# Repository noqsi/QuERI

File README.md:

# QuERI
Electronics for X-ray fluorescence measurements

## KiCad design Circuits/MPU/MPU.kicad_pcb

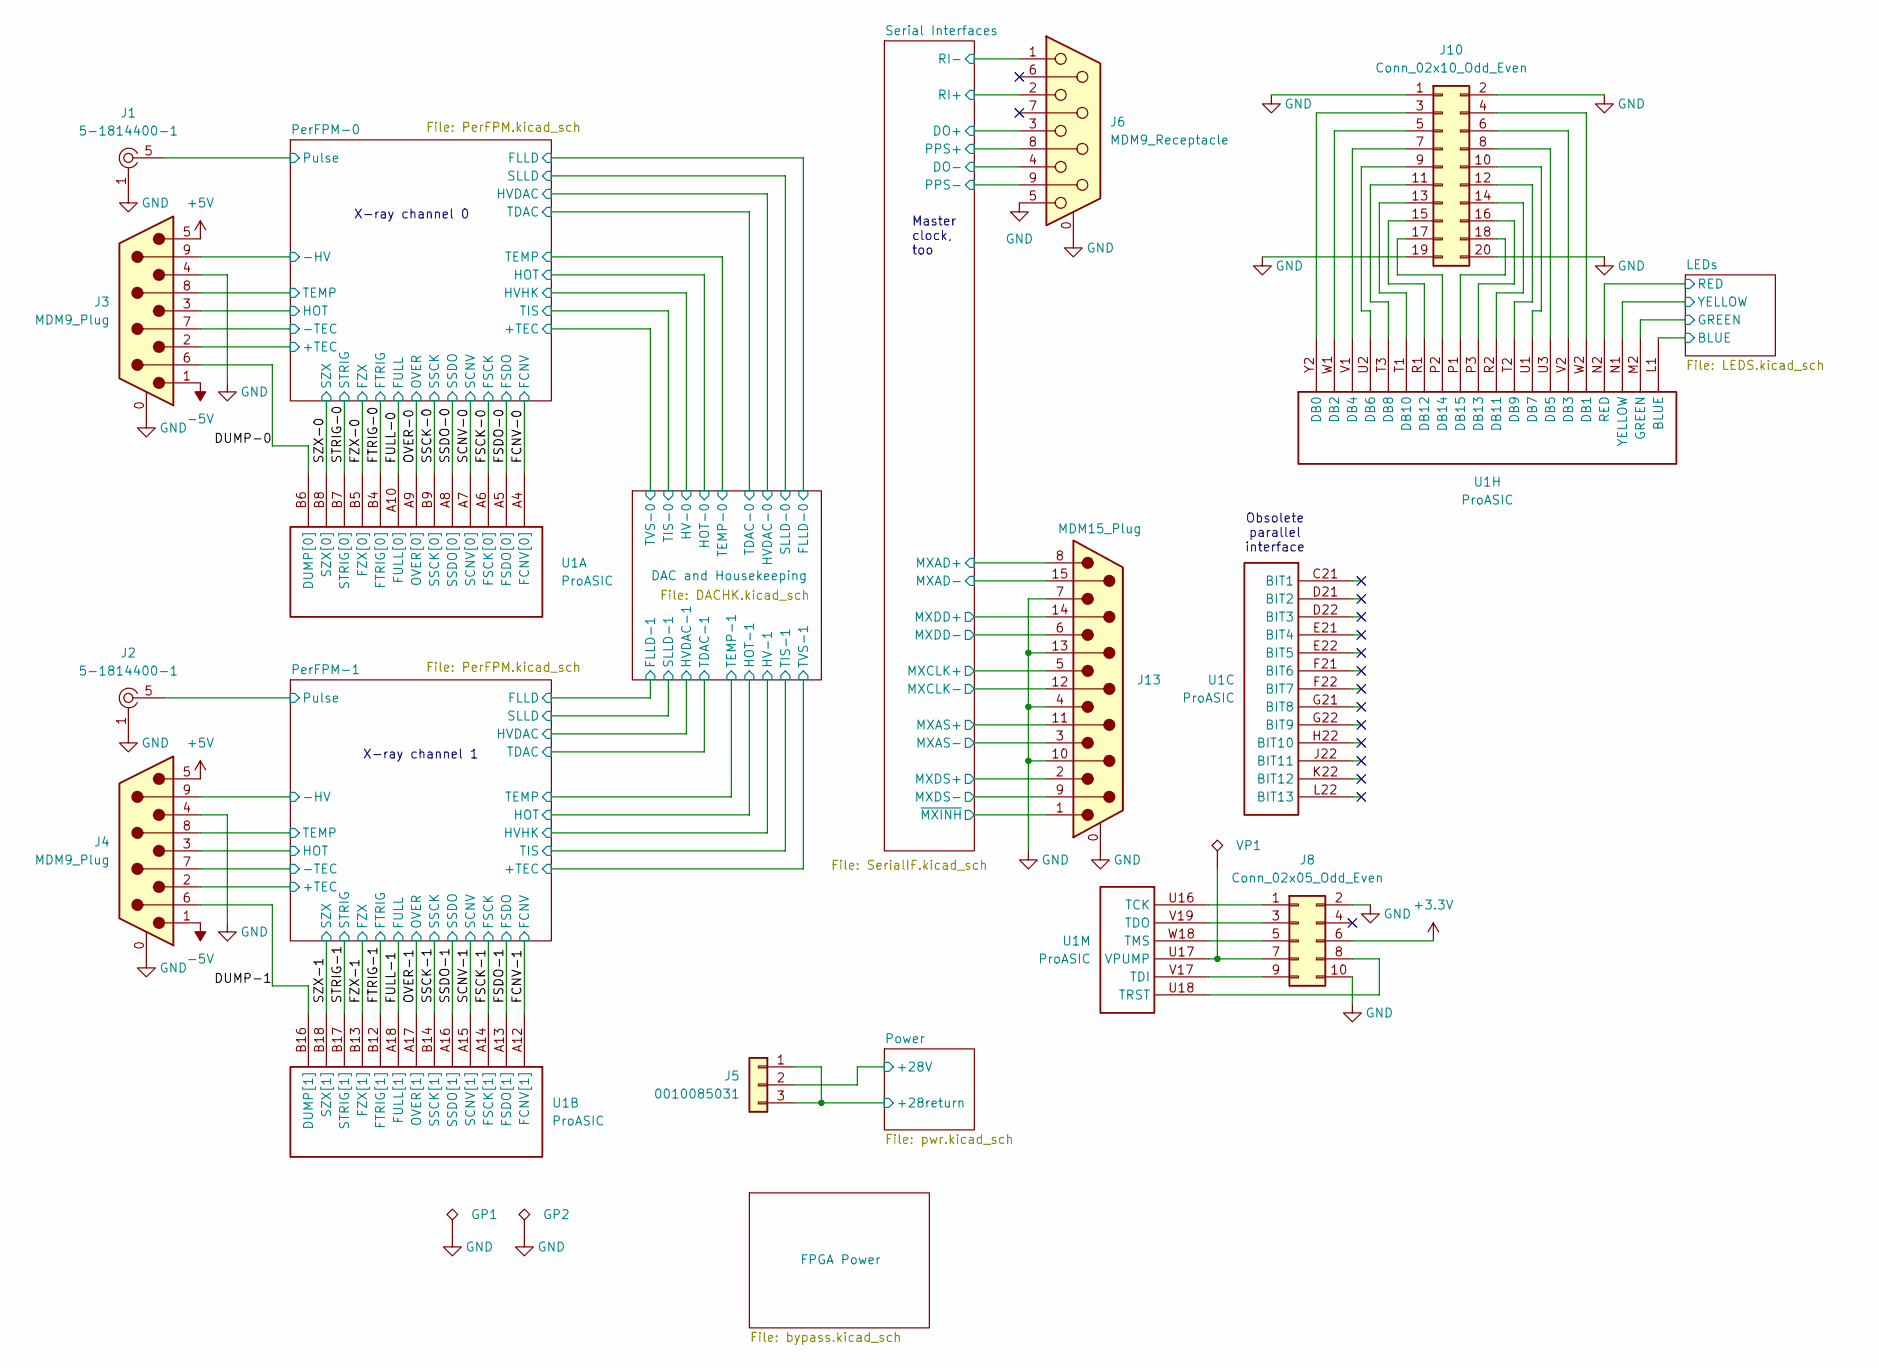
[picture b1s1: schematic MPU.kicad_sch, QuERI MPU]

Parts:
GP1, GP2: TestPoint_Alt; TestPoint_Keystone_5015_Micro_Mini
J1, J2: 5-1814400-1; RF_SMA_RightAngle_5-1814400-1; MPN 5-1814400-1; Digi-Key_PN A97593-ND
J3, J4: MDM9_Plug; ITT_MDM-9SCBRP
J5: 0010085031; Molex_KK-396_A-41791-0003_1x03_P3.96mm_Vertical
J6: MDM9_Receptacle; ITT_MDM-9SCBRP
J8: Conn_02x05_Odd_Even; PinHeader_2x05_P2.54mm_Vertical
J10: Conn_02x10_Odd_Even; PinHeader_2x10_P2.54mm_Vertical
J13: MDM15_Plug; ITT_MDM-15PCBR
U1: ProASIC; BGA-484_23.0x23.0mm_Layout22x22_P1.0mm
VP1: TestPoint_Alt; TestPoint_Keystone_5015_Micro_Mini

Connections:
+3.3V: J8.6; also elsewhere on the board
+5V: J3.5, J4.5; also elsewhere on the board
-5V: J3.1, J4.1; also elsewhere on the board
/DAC and Housekeeping/HOT-0: J3.3; also elsewhere on the board
/DAC and Housekeeping/HOT-1: J4.3; also elsewhere on the board
/DAC and Housekeeping/TEMP-0: J3.8; also elsewhere on the board
/DAC and Housekeeping/TEMP-1: J4.8; also elsewhere on the board
/DAC and Housekeeping/TVS-0: J3.2; also elsewhere on the board
/DAC and Housekeeping/TVS-1: J4.2; also elsewhere on the board
/DUMP-0: J3.6, U1.B6 (DUMP[0])
/DUMP-1: J4.6, U1.B16 (DUMP[1])
/FCNV-0: U1.A4 (FCNV[0]); also elsewhere on the board
/FCNV-1: U1.A12 (FCNV[1]); also elsewhere on the board
/FSCK-0: U1.A6 (FSCK[0]); also elsewhere on the board
/FSCK-1: U1.A14 (FSCK[1]); also elsewhere on the board
/FSDO-0: U1.A5 (FSDO[0]); also elsewhere on the board
/FSDO-1: U1.A13 (FSDO[1]); also elsewhere on the board
/FTRIG-0: U1.B4 (FTRIG[0]); also elsewhere on the board
/FTRIG-1: U1.B12 (FTRIG[1]); also elsewhere on the board
/FULL-0: U1.A10 (FULL[0]); also elsewhere on the board
/FULL-1: U1.A18 (FULL[1]); also elsewhere on the board
/FZX-0: U1.B5 (FZX[0]); also elsewhere on the board
/FZX-1: U1.B13 (FZX[1]); also elsewhere on the board
/LEDs/BLUE: U1.L1 (BLUE); also elsewhere on the board
/LEDs/GREEN: U1.M2 (GREEN); also elsewhere on the board
/LEDs/RED: U1.N2 (RED); also elsewhere on the board
/LEDs/YELLOW: U1.N1 (YELLOW); also elsewhere on the board
/OVER-0: U1.A9 (OVER[0]); also elsewhere on the board
/OVER-1: U1.A17 (OVER[1]); also elsewhere on the board
/PerFPM-0/-HV: J3.9; also elsewhere on the board
/PerFPM-0/-TEC: J3.7; also elsewhere on the board
/PerFPM-0/Pulse: J1.5; also elsewhere on the board
/PerFPM-1/-HV: J4.9; also elsewhere on the board
/PerFPM-1/-TEC: J4.7; also elsewhere on the board
/PerFPM-1/Pulse: J2.5; also elsewhere on the board
/Power/+28V: J5.2; also elsewhere on the board
/Power/+28return: J5.1, J5.3; also elsewhere on the board
/SCNV-0: U1.A7 (SCNV[0]); also elsewhere on the board
/SCNV-1: U1.A15 (SCNV[1]); also elsewhere on the board
/SSCK-0: U1.B9 (SSCK[0]); also elsewhere on the board
/SSCK-1: U1.B14 (SSCK[1]); also elsewhere on the board
/SSDO-0: U1.A8 (SSDO[0]); also elsewhere on the board
/SSDO-1: U1.A16 (SSDO[1]); also elsewhere on the board
/STRIG-0: U1.B7 (STRIG[0]); also elsewhere on the board
/STRIG-1: U1.B17 (STRIG[1]); also elsewhere on the board
/SZX-0: U1.B8 (SZX[0]); also elsewhere on the board
/SZX-1: U1.B18 (SZX[1]); also elsewhere on the board
/Serial Interfaces/DO+: J6.3; also elsewhere on the board
/Serial Interfaces/DO-: J6.4; also elsewhere on the board
/Serial Interfaces/MXAD+: J13.8; also elsewhere on the board
/Serial Interfaces/MXAD-: J13.15; also elsewhere on the board
/Serial Interfaces/MXAS+: J13.11 (P111); also elsewhere on the board
/Serial Interfaces/MXAS-: J13.3; also elsewhere on the board
/Serial Interfaces/MXCLK+: J13.5; also elsewhere on the board
/Serial Interfaces/MXCLK-: J13.12; also elsewhere on the board
/Serial Interfaces/MXDD+: J13.14; also elsewhere on the board
/Serial Interfaces/MXDD-: J13.6; also elsewhere on the board
/Serial Interfaces/MXDS+: J13.2; also elsewhere on the board
/Serial Interfaces/MXDS-: J13.9; also elsewhere on the board
/Serial Interfaces/PPS+: J6.8; also elsewhere on the board
/Serial Interfaces/PPS-: J6.9; also elsewhere on the board
/Serial Interfaces/RI+: J6.2; also elsewhere on the board
/Serial Interfaces/RI-: J6.1; also elsewhere on the board
/Serial Interfaces/~MXINH: J13.1; also elsewhere on the board
GND: GP1.1, GP2.1, J1.1, J2.1, J3.0 (PAD), J3.4, J4.0 (PAD), J4.4, J6.0 (PAD), J6.5, J8.2, J8.10, J10.1, J10.2, J10.19, J10.20, J13.0 (PAD), J13.4, J13.7, J13.10, J13.13; also elsewhere on the board
unnamed: J8.1, U1.U16 (TCK)
unnamed: J8.3, U1.V19 (TDO)
unnamed: J8.5, U1.W18 (TMS)
unnamed: J8.7, U1.U17 (VPUMP), VP1.1
unnamed: J8.8, U1.U18 (TRST)
unnamed: J8.9, U1.V17 (TDI)
unnamed: J10.3, U1.Y2 (DB0)
unnamed: J10.4, U1.W2 (DB1)
unnamed: J10.5, U1.W1 (DB2)
unnamed: J10.6, U1.V2 (DB3)
unnamed: J10.7, U1.V1 (DB4)
unnamed: J10.8, U1.U3 (DB5)
unnamed: J10.9, U1.U2 (DB6)
unnamed: J10.10, U1.U1 (DB7)
unnamed: J10.11, U1.T3 (DB8)
unnamed: J10.12, U1.T2 (DB9)
unnamed: J10.13, U1.T1 (DB10)
unnamed: J10.14, U1.R2 (DB11)
unnamed: J10.15, U1.R1 (DB12)
unnamed: J10.16, U1.P3 (DB13)
unnamed: J10.17, U1.P2 (DB14)
unnamed: J10.18, U1.P1 (DB15)

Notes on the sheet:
X-ray channel 0
X-ray channel 1
Obsolete parallel interface
Master clock, too

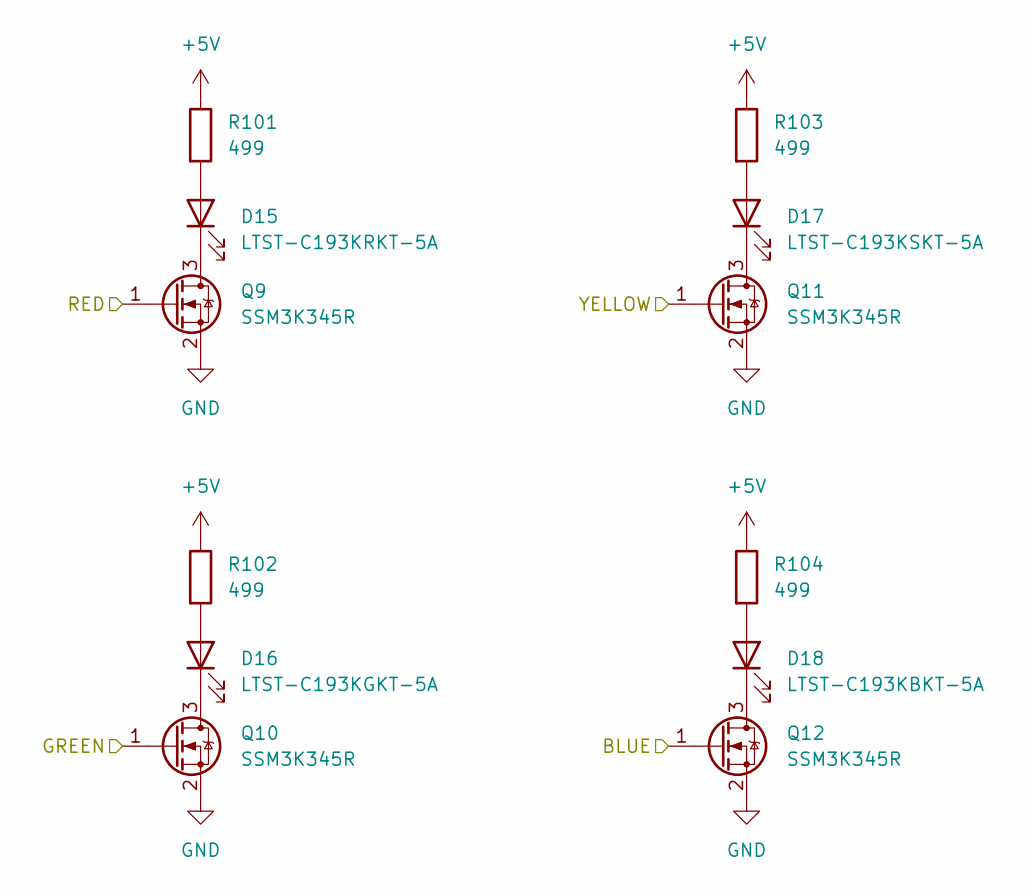
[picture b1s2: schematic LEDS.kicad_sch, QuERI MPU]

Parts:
D15: LTST-C193KRKT-5A; LED_0603_1608Metric
D16: LTST-C193KGKT-5A; LED_0603_1608Metric
D17: LTST-C193KSKT-5A; LED_0603_1608Metric
D18: LTST-C193KBKT-5A; LED_0603_1608Metric
Q9, Q10, Q11, Q12: SSM3K345R; SOT-23
R101, R102, R103, R104: 499; R_0603_1608Metric

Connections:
+5V: R101.1, R102.1, R103.1, R104.1; also elsewhere on the board
/LEDs/BLUE: Q12.1 (G); also elsewhere on the board
/LEDs/GREEN: Q10.1 (G); also elsewhere on the board
/LEDs/RED: Q9.1 (G); also elsewhere on the board
/LEDs/YELLOW: Q11.1 (G); also elsewhere on the board
GND: Q9.2 (S), Q10.2 (S), Q11.2 (S), Q12.2 (S); also elsewhere on the board
unnamed: D15.2 (A), R101.2
unnamed: D15.1 (K), Q9.3 (D)
unnamed: D16.2 (A), R102.2
unnamed: D16.1 (K), Q10.3 (D)
unnamed: D17.2 (A), R103.2
unnamed: D17.1 (K), Q11.3 (D)
unnamed: D18.2 (A), R104.2
unnamed: D18.1 (K), Q12.3 (D)

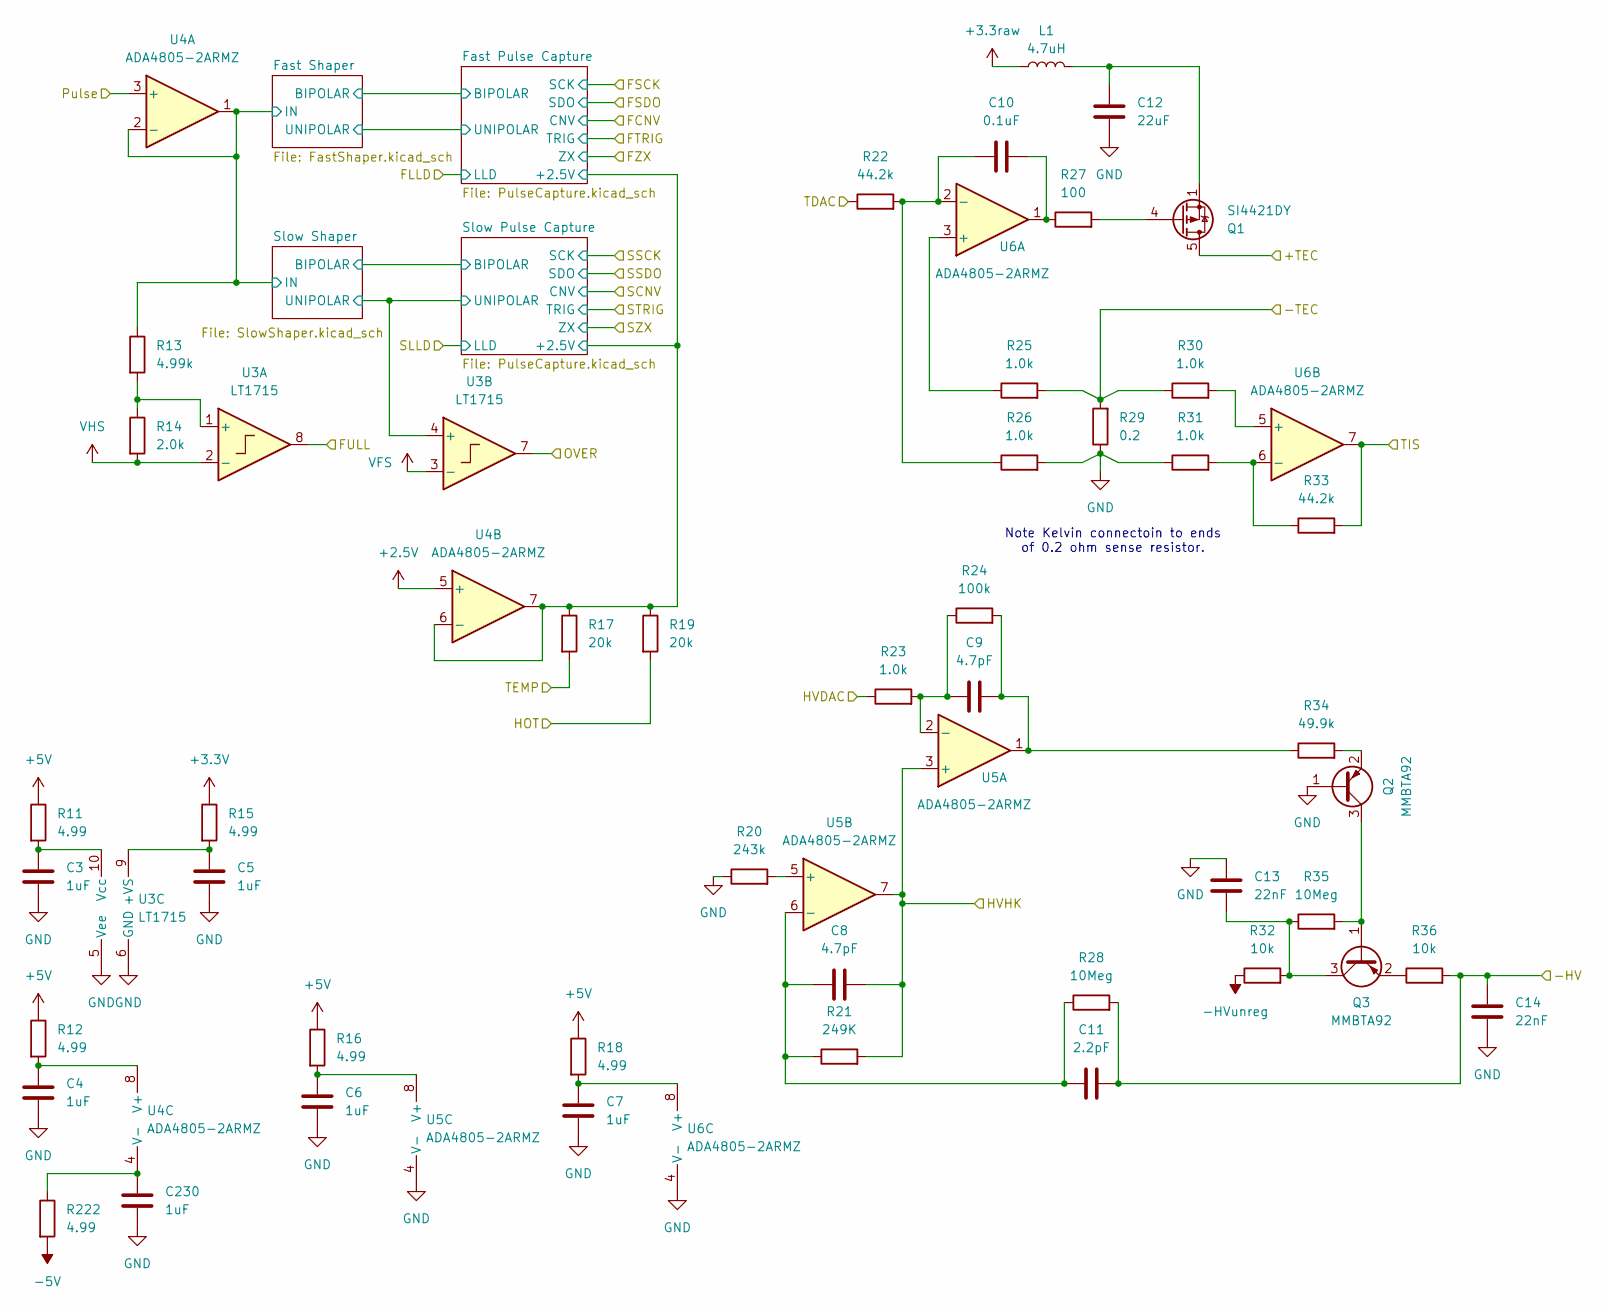
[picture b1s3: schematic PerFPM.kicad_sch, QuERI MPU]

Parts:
C3, C4, C5, C6, C7, C230: 1uF; C_0805_2012Metric
C8, C9: 4.7pF; C_0603_1608Metric
C10: 0.1uF; C_0603_1608Metric
C11: 2.2pF; C_1206_3216Metric
C12: 22uF; C_1210_3225Metric
C13, C14: 22nF; C_1210_3225Metric
L1: 4.7uH; L_1008_2520Metric
Q1: SI4421DY; SOIC-8_3.9x4.9mm_P1.27mm
Q2, Q3: MMBTA92; SOT-23
R11, R12, R15, R16, R18, R222: 4.99; R_0603_1608Metric
R13: 4.99k; R_0603_1608Metric
R14: 2.0k; R_0603_1608Metric
R17, R19: 20k; R_0603_1608Metric
R20: 243k; R_0603_1608Metric
R21: 249K; R_0603_1608Metric
R22, R33: 44.2k; R_0603_1608Metric
R23, R25, R26, R30, R31: 1.0k; R_0603_1608Metric
R24: 100k; R_0603_1608Metric
R27: 100; R_0603_1608Metric
R28, R35: 10Meg; R_2010_5025Metric
R29: 0.2; R_0805_2012Metric
R32, R36: 10k; R_0603_1608Metric
R34: 49.9k; R_0603_1608Metric
U3: LT1715; MSOP-10_3x3mm_P0.5mm
U4, U5, U6: ADA4805-2ARMZ; MSOP-8_3x3mm_P0.65mm

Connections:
+2.5V: U4.5 (+); also elsewhere on the board
+3.3V: R15.1; also elsewhere on the board
+3.3raw: L1.1; also elsewhere on the board
+5V: R11.1, R12.1, R16.1, R18.1; also elsewhere on the board
-5V: R222.2; also elsewhere on the board
-HVunreg: R32.1; also elsewhere on the board
/DAC and Housekeeping/HOT-0: R19.2; also elsewhere on the board
/DAC and Housekeeping/HV-0: C8.2, R21.2, U5.3 (+), U5.7; also elsewhere on the board
/DAC and Housekeeping/HVDAC-0: R23.1; also elsewhere on the board
/DAC and Housekeeping/TDAC-0: R22.1; also elsewhere on the board
/DAC and Housekeeping/TEMP-0: R17.2; also elsewhere on the board
/DAC and Housekeeping/TIS-0: R33.2, U6.7; also elsewhere on the board
/DAC and Housekeeping/TVS-0: Q1.5 (D), Q1.6 (D), Q1.7 (D), Q1.8 (D); also elsewhere on the board
/FULL-0: U3.8; also elsewhere on the board
/OVER-0: U3.7; also elsewhere on the board
/PerFPM-0/-HV: C11.2, C14.1, R28.2, R36.2; also elsewhere on the board
/PerFPM-0/-TEC: R25.2, R29.2, R30.1; also elsewhere on the board
/PerFPM-0/Fast Pulse Capture/+2.5V: R17.1, R19.1, U4.6 (-), U4.7; also elsewhere on the board
/PerFPM-0/Fast Shaper/IN: R13.1, U4.1, U4.2 (-); also elsewhere on the board
/PerFPM-0/Pulse: U4.3 (+); also elsewhere on the board
/PerFPM-0/Slow Pulse Capture/UNIPOLAR: U3.4 (+); also elsewhere on the board
GND: C3.2, C4.2, C5.2, C6.2, C7.2, C12.2, C13.1, C14.2, C230.2, Q2.1 (B), R20.1, R26.2, R29.1, R31.1, U3.5 (Vee), U3.6 (GND), U5.4 (V-), U6.4 (V-); also elsewhere on the board
unnamed: C9.2, R24.2, R34.1, U5.1
unnamed: C10.1, R27.1, U6.1
unnamed: C12.1, L1.2, Q1.1 (S), Q1.2 (S), Q1.3 (S)
unnamed: Q1.4 (G), R27.2
unnamed: Q2.3 (C), Q3.1 (B), R35.2
unnamed: Q2.2 (E), R34.2
unnamed: C13.2, Q3.3 (C), R32.2, R35.1
unnamed: Q3.2 (E), R36.1
unnamed: R13.2, R14.1, U3.1 (+)
unnamed: C5.1, R15.2, U3.9 (+VS)
unnamed: C3.1, R11.2, U3.10 (Vcc)
unnamed: C4.1, R12.2, U4.8 (V+)
unnamed: C230.1, R222.1, U4.4 (V-)
unnamed: C9.1, R23.2, R24.1, U5.2 (-)
unnamed: R20.2, U5.5 (+)
unnamed: C8.1, C11.1, R21.1, R28.1, U5.6 (-)
unnamed: C6.1, R16.2, U5.8 (V+)
unnamed: R25.1, U6.3 (+)
unnamed: C10.2, R22.2, R26.1, U6.2 (-)
unnamed: R30.2, U6.5 (+)
unnamed: R31.2, R33.1, U6.6 (-)
unnamed: C7.1, R18.2, U6.8 (V+)
VFS: U3.3 (-); also elsewhere on the board
VHS: R14.2, U3.2 (-); also elsewhere on the board

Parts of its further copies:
C15, C16, C17, C18, C19, C231: 1uF; C_0805_2012Metric
C20, C21: 4.7pF; C_0603_1608Metric
C22: 0.1uF; C_0603_1608Metric
C23: 2.2pF; C_1206_3216Metric
C24: 22uF; C_1210_3225Metric
C25, C26: 22nF; C_1210_3225Metric
L2: 4.7uH; L_1008_2520Metric
Q4: SI4421DY; SOIC-8_3.9x4.9mm_P1.27mm
Q5, Q6: MMBTA92; SOT-23
R37, R38, R41, R42, R44, R236: 4.99; R_0603_1608Metric
R39: 4.99k; R_0603_1608Metric
R40: 2.0k; R_0603_1608Metric
R43, R45: 20k; R_0603_1608Metric
R46: 243k; R_0603_1608Metric
R47: 249K; R_0603_1608Metric
R48, R59: 44.2k; R_0603_1608Metric
R49, R51, R52, R56, R57: 1.0k; R_0603_1608Metric
R50: 100k; R_0603_1608Metric
R53: 100; R_0603_1608Metric
R54, R61: 10Meg; R_2010_5025Metric
R55: 0.2; R_0805_2012Metric
R58, R62: 10k; R_0603_1608Metric
R60: 49.9k; R_0603_1608Metric
U7: LT1715; MSOP-10_3x3mm_P0.5mm
U8, U9, U10: ADA4805-2ARMZ; MSOP-8_3x3mm_P0.65mm

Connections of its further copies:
+2.5V: U8.5 (+); also elsewhere on the board
+3.3V: R41.1; also elsewhere on the board
+3.3raw: L2.1; also elsewhere on the board
+5V: R37.1, R38.1, R42.1, R44.1; also elsewhere on the board
-5V: R236.2; also elsewhere on the board
-HVunreg: R58.1; also elsewhere on the board
/DAC and Housekeeping/HOT-1: R45.2; also elsewhere on the board
/DAC and Housekeeping/HV-1: C20.2, R47.2, U9.3 (+), U9.7; also elsewhere on the board
/DAC and Housekeeping/HVDAC-1: R49.1; also elsewhere on the board
/DAC and Housekeeping/TDAC-1: R48.1; also elsewhere on the board
/DAC and Housekeeping/TEMP-1: R43.2; also elsewhere on the board
/DAC and Housekeeping/TIS-1: R59.2, U10.7; also elsewhere on the board
/DAC and Housekeeping/TVS-1: Q4.5 (D), Q4.6 (D), Q4.7 (D), Q4.8 (D); also elsewhere on the board
/FULL-1: U7.8; also elsewhere on the board
/OVER-1: U7.7; also elsewhere on the board
/PerFPM-1/-HV: C23.2, C26.1, R54.2, R62.2; also elsewhere on the board
/PerFPM-1/-TEC: R51.2, R55.2, R56.1; also elsewhere on the board
/PerFPM-1/Fast Pulse Capture/+2.5V: R43.1, R45.1, U8.6 (-), U8.7; also elsewhere on the board
/PerFPM-1/Fast Shaper/IN: R39.1, U8.1, U8.2 (-); also elsewhere on the board
/PerFPM-1/Pulse: U8.3 (+); also elsewhere on the board
/PerFPM-1/Slow Pulse Capture/UNIPOLAR: U7.4 (+); also elsewhere on the board
GND: C15.2, C16.2, C17.2, C18.2, C19.2, C24.2, C25.1, C26.2, C231.2, Q5.1 (B), R46.1, R52.2, R55.1, R57.1, U7.5 (Vee), U7.6 (GND), U9.4 (V-), U10.4 (V-); also elsewhere on the board
unnamed: C21.2, R50.2, R60.1, U9.1
unnamed: C22.1, R53.1, U10.1
unnamed: C24.1, L2.2, Q4.1 (S), Q4.2 (S), Q4.3 (S)
unnamed: Q4.4 (G), R53.2
unnamed: Q5.3 (C), Q6.1 (B), R61.2
unnamed: Q5.2 (E), R60.2
unnamed: C25.2, Q6.3 (C), R58.2, R61.1
unnamed: Q6.2 (E), R62.1
unnamed: R39.2, R40.1, U7.1 (+)
unnamed: C17.1, R41.2, U7.9 (+VS)
unnamed: C15.1, R37.2, U7.10 (Vcc)
unnamed: C16.1, R38.2, U8.8 (V+)
unnamed: C231.1, R236.1, U8.4 (V-)
unnamed: C21.1, R49.2, R50.1, U9.2 (-)
unnamed: R46.2, U9.5 (+)
unnamed: C20.1, C23.1, R47.1, R54.1, U9.6 (-)
unnamed: C18.1, R42.2, U9.8 (V+)
unnamed: R51.1, U10.3 (+)
unnamed: C22.2, R48.2, R52.1, U10.2 (-)
unnamed: R56.2, U10.5 (+)
unnamed: R57.2, R59.1, U10.6 (-)
unnamed: C19.1, R44.2, U10.8 (V+)
VFS: U7.3 (-); also elsewhere on the board
VHS: R40.2, U7.2 (-); also elsewhere on the board

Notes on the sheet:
Note Kelvin connectoin to ends of 0.2 ohm sense resistor.

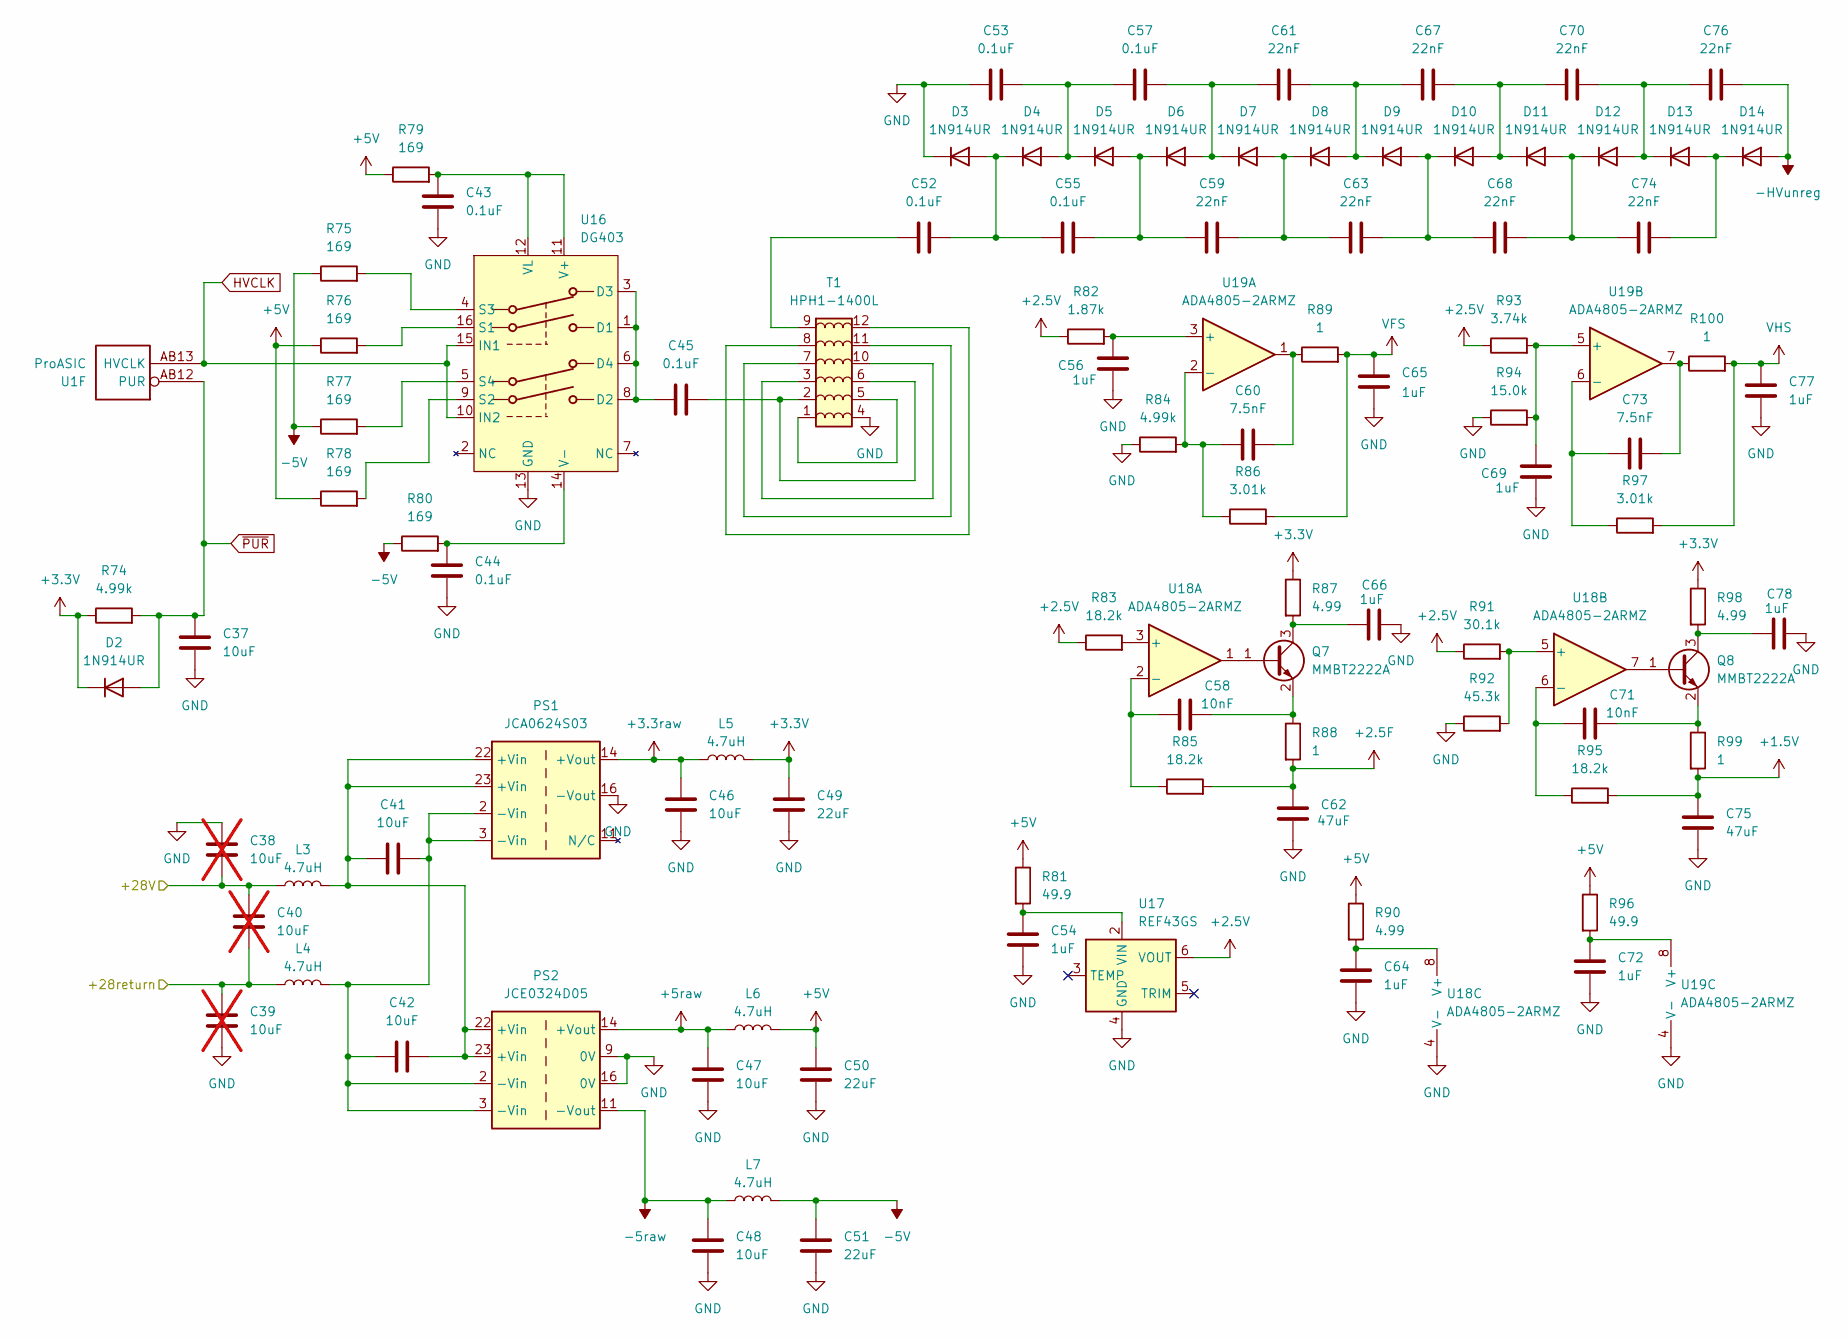
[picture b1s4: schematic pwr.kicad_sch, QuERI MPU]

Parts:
C37: 10uF; C_0805_2012Metric
C38, C39, C40: 10uF; C_1210_3225Metric; not fitted
C41, C42, C46, C47, C48: 10uF; C_1210_3225Metric
C43, C44, C45, C52, C53, C55, C57: 0.1uF; C_0603_1608Metric
C49, C50, C51: 22uF; C_1210_3225Metric
C54, C56, C64, C65, C66, C69, C72, C77, C78: 1uF; C_0805_2012Metric
C58, C71: 10nF; C_0603_1608Metric
C59, C61, C63, C67, C68, C70, C74, C76: 22nF; C_0603_1608Metric
C60, C73: 7.5nF; C_0603_1608Metric
C62, C75: 47uF; C_1210_3225Metric
D2, D3, D4, D5, D6, D7, D8, D9, D10, D11, D12, D13, D14: 1N914UR; D_MiniMELF
L3, L4, L5, L6, L7: 4.7uH; L_1008_2520Metric
PS1: JCA0624S03; JCA04-06_SINGLEOUTPUT_XPR
PS2: JCE0324D05; JCE03-05_DUALOUTPUT
Q7, Q8: MMBT2222A; SOT-23
R74, R84: 4.99k; R_0603_1608Metric
R75, R76, R77, R78, R79, R80: 169; R_1206_3216Metric
R81, R96: 49.9; R_0603_1608Metric
R82: 1.87k; R_0603_1608Metric
R83, R85, R95: 18.2k; R_0603_1608Metric
R86, R97: 3.01k; R_0603_1608Metric
R87, R90, R98: 4.99; R_0603_1608Metric
R88, R89, R99, R100: 1; R_0603_1608Metric
R91: 30.1k; R_0603_1608Metric
R92: 45.3k; R_0603_1608Metric
R93: 3.74k; R_0603_1608Metric
R94: 15.0k; R_0603_1608Metric
T1: HPH1-1400L
U1: ProASIC; BGA-484_23.0x23.0mm_Layout22x22_P1.0mm
U16: DG403; SOIC-16_3.9x9.9mm_P1.27mm
U17: REF43GS; SOIC-8_3.9x4.9mm_P1.27mm
U18, U19: ADA4805-2ARMZ; MSOP-8_3x3mm_P0.65mm

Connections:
+1.5V: C75.1, R95.2, R99.2; also elsewhere on the board
+2.5F: C62.1, R85.2, R88.2; also elsewhere on the board
+2.5V: R82.1, R83.1, R91.1, R93.1, U17.6 (VOUT); also elsewhere on the board
+3.3V: C49.1, D2.1 (K), L5.2, R74.1, R87.1, R98.1; also elsewhere on the board
+3.3raw: C46.1, L5.1, PS1.14 (+Vout); also elsewhere on the board
+5V: C50.1, L6.2, R76.1, R78.1, R79.1, R81.1, R90.1, R96.1; also elsewhere on the board
+5raw: C47.1, L6.1, PS2.14 (+Vout)
-5V: C51.1, L7.2, R75.1, R77.1, R80.1; also elsewhere on the board
-5raw: C48.1, L7.1, PS2.11 (-Vout)
-HVunreg: C76.2, D14.2 (A); also elsewhere on the board
/Power/+28V: C38.2, C40.1, L3.1; also elsewhere on the board
/Power/+28return: C39.1, C40.2, L4.1; also elsewhere on the board
GND: C37.2, C38.1, C39.2, C43.2, C44.2, C46.2, C47.2, C48.2, C49.2, C50.2, C51.2, C53.1, C54.2, C56.2, C62.2, C64.2, C65.2, C66.2, C69.2, C72.2, C75.2, C77.2, C78.2, D3.1 (K), PS1.16 (-Vout), PS2.9 (0V), PS2.16 (0V), R84.1, R92.1, R94.1, T1.4, U16.13 (GND), U17.4 (GND), U18.4 (V-), U19.4 (V-); also elsewhere on the board
HVCLK: U1.AB13 (HVCLK), U16.10 (IN2), U16.15 (IN1)
unnamed: C41.1, C42.2, L3.2, PS1.22 (+Vin), PS1.23 (+Vin), PS2.22 (+Vin), PS2.23 (+Vin)
unnamed: C41.2, C42.1, L4.2, PS1.2 (-Vin), PS1.3 (-Vin), PS2.2 (-Vin), PS2.3 (-Vin)
unnamed: C45.2, T1.2, T1.6
unnamed: C52.1, T1.9
unnamed: C60.1, R89.1, U19.1
unnamed: C73.1, R100.1, U19.7
unnamed: C52.2, C55.1, D3.2 (A), D4.1 (K)
unnamed: C53.2, C57.1, D4.2 (A), D5.1 (K)
unnamed: C55.2, C59.1, D5.2 (A), D6.1 (K)
unnamed: C57.2, C61.1, D6.2 (A), D7.1 (K)
unnamed: C59.2, C63.1, D7.2 (A), D8.1 (K)
unnamed: C61.2, C67.1, D8.2 (A), D9.1 (K)
unnamed: C67.2, C70.1, D10.2 (A), D11.1 (K)
unnamed: C63.2, C68.1, D9.2 (A), D10.1 (K)
unnamed: C68.2, C74.1, D11.2 (A), D12.1 (K)
unnamed: C70.2, C76.1, D12.2 (A), D13.1 (K)
unnamed: C74.2, D13.2 (A), D14.1 (K)
unnamed: Q7.1 (B), U18.1
unnamed: C66.1, Q7.3 (C), R87.2
unnamed: C58.1, Q7.2 (E), R88.1
unnamed: Q8.1 (B), U18.7
unnamed: C78.1, Q8.3 (C), R98.2
unnamed: C71.1, Q8.2 (E), R99.1
unnamed: T1.1, T1.5
unnamed: T1.3, T1.10
unnamed: T1.7, T1.11
unnamed: T1.8, T1.12
unnamed: C45.1, U16.1 (D1), U16.3 (D3), U16.6 (D4), U16.8 (D2)
unnamed: R76.2, U16.16 (S1)
unnamed: R78.2, U16.9 (S2)
unnamed: R75.2, U16.4 (S3)
unnamed: R77.2, U16.5 (S4)
unnamed: C43.1, R79.2, U16.11 (V+), U16.12 (VL)
unnamed: C44.1, R80.2, U16.14 (V-)
unnamed: C54.1, R81.2, U17.2 (VIN)
unnamed: R83.2, U18.3 (+)
unnamed: C58.2, R85.1, U18.2 (-)
unnamed: R91.2, R92.2, U18.5 (+)
unnamed: C71.2, R95.1, U18.6 (-)
unnamed: C64.1, R90.2, U18.8 (V+)
unnamed: C56.1, R82.2, U19.3 (+)
unnamed: C60.2, R84.2, R86.1, U19.2 (-)
unnamed: C69.1, R93.2, R94.2, U19.5 (+)
unnamed: C73.2, R97.1, U19.6 (-)
unnamed: C72.1, R96.2, U19.8 (V+)
VFS: C65.1, R86.2, R89.2; also elsewhere on the board
VHS: C77.1, R97.2, R100.2; also elsewhere on the board
~PUR: C37.1, D2.2 (A), R74.2, U1.AB12 (PUR)

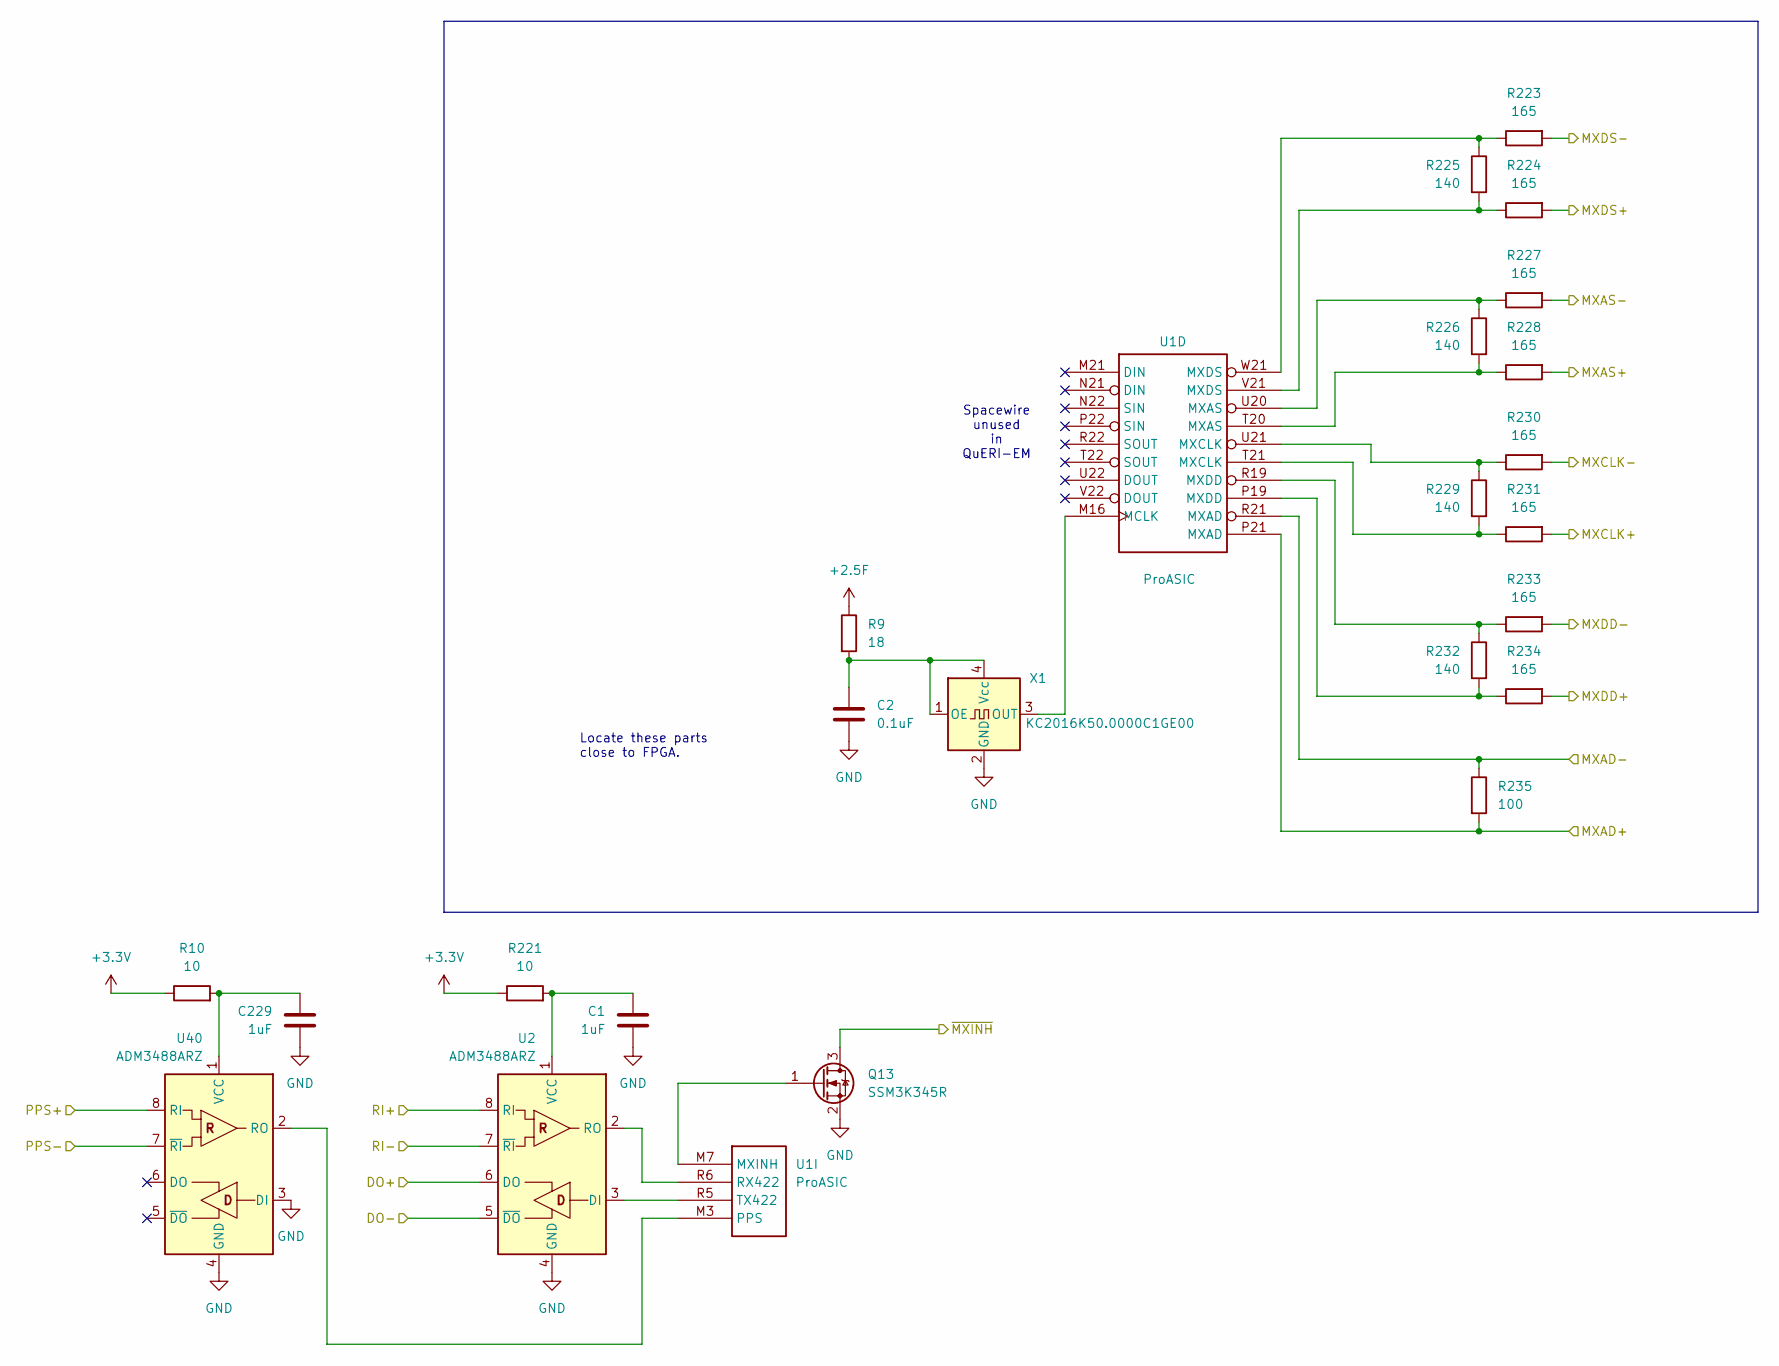
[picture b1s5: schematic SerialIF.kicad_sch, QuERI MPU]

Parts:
C1, C229: 1uF; C_0805_2012Metric
C2: 0.1uF; C_0603_1608Metric
Q13: SSM3K345R; SOT-23
R9: 18; R_0603_1608Metric
R10, R221: 10; R_2512_6332Metric
R223, R224, R227, R228, R230, R231, R233, R234: 165; R_0603_1608Metric
R225, R226, R229, R232: 140; R_0603_1608Metric
R235: 100; R_0603_1608Metric
U1: ProASIC; BGA-484_23.0x23.0mm_Layout22x22_P1.0mm
U2, U40: ADM3488ARZ; SOIC-8_3.9x4.9mm_P1.27mm
X1: KC2016K50.0000C1GE00; Oscillator_SMD_SeikoEpson_SG210-4Pin_2.5x2.0mm

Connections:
+2.5F: R9.1; also elsewhere on the board
+3.3V: R10.1, R221.1; also elsewhere on the board
/Serial Interfaces/DO+: U2.6 (DO); also elsewhere on the board
/Serial Interfaces/DO-: U2.5 (~DO); also elsewhere on the board
/Serial Interfaces/MXAD+: R235.2, U1.P21 (MXAD); also elsewhere on the board
/Serial Interfaces/MXAD-: R235.1, U1.R21 (MXAD); also elsewhere on the board
/Serial Interfaces/MXAS+: R228.2; also elsewhere on the board
/Serial Interfaces/MXAS-: R227.2; also elsewhere on the board
/Serial Interfaces/MXCLK+: R231.2; also elsewhere on the board
/Serial Interfaces/MXCLK-: R230.2; also elsewhere on the board
/Serial Interfaces/MXDD+: R234.2; also elsewhere on the board
/Serial Interfaces/MXDD-: R233.2; also elsewhere on the board
/Serial Interfaces/MXDS+: R224.2; also elsewhere on the board
/Serial Interfaces/MXDS-: R223.2; also elsewhere on the board
/Serial Interfaces/PPS+: U40.8 (RI); also elsewhere on the board
/Serial Interfaces/PPS-: U40.7 (~RI); also elsewhere on the board
/Serial Interfaces/RI+: U2.8 (RI); also elsewhere on the board
/Serial Interfaces/RI-: U2.7 (~RI); also elsewhere on the board
/Serial Interfaces/~MXINH: Q13.3 (D); also elsewhere on the board
GND: C1.2, C2.2, C229.2, Q13.2 (S), U2.4 (GND), U40.3 (DI), U40.4 (GND), X1.2 (GND); also elsewhere on the board
unnamed: Q13.1 (G), U1.M7 (MXINH)
unnamed: R223.1, R225.1, U1.W21 (MXDS)
unnamed: R224.1, R225.2, U1.V21 (MXDS)
unnamed: R226.1, R227.1, U1.U20 (MXAS)
unnamed: R226.2, R228.1, U1.T20 (MXAS)
unnamed: R229.1, R230.1, U1.U21 (MXCLK)
unnamed: R229.2, R231.1, U1.T21 (MXCLK)
unnamed: R232.1, R233.1, U1.R19 (MXDD)
unnamed: R232.2, R234.1, U1.P19 (MXDD)
unnamed: U1.M16 (MCLK), X1.3 (OUT)
unnamed: U1.M3 (PPS), U40.2 (RO)
unnamed: U1.R6 (RX422), U2.2 (RO)
unnamed: U1.R5 (TX422), U2.3 (DI)
unnamed: C1.1, R221.2, U2.1 (VCC)
unnamed: C229.1, R10.2, U40.1 (VCC)
unnamed: C2.1, R9.2, X1.1 (OE), X1.4 (Vcc)

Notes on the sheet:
Locate these parts close to FPGA.
Spacewire unused in QuERI-EM
